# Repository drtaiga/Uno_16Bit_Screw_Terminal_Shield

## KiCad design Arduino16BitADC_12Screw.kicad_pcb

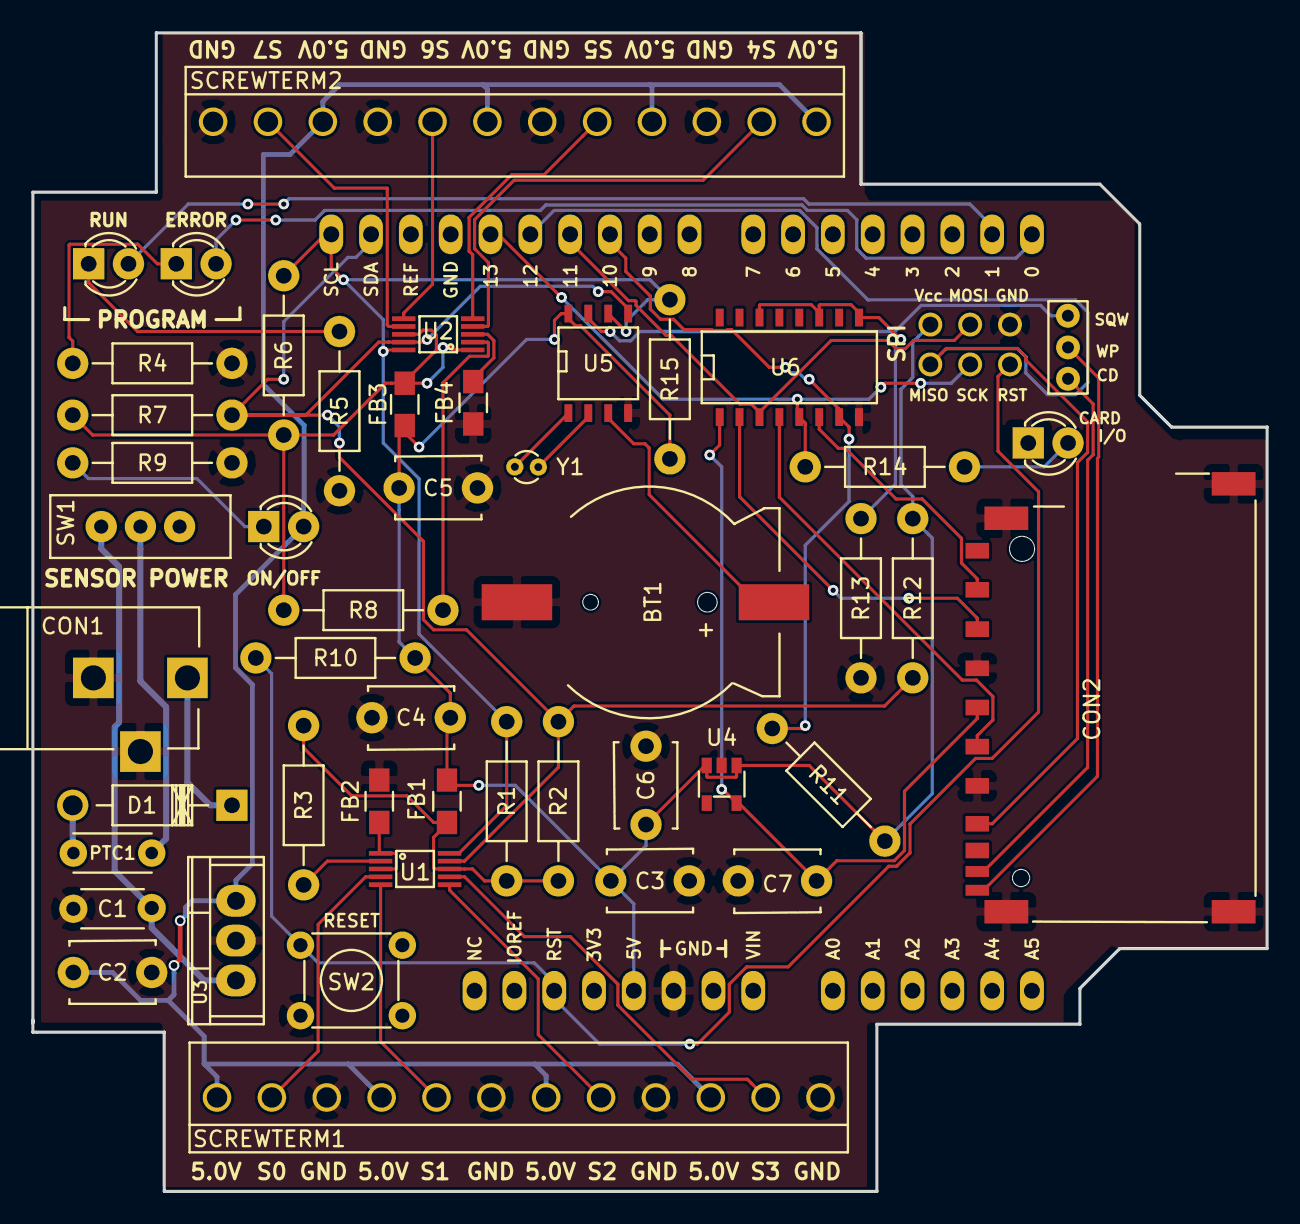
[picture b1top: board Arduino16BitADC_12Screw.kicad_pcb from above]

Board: 2 copper layers, 78.7 x 73.9 mm, 48 parts (0 on the bottom side), 45 nets.

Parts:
BT1: CR1220; Coin_Cell_Batt_12mm
C1: 0.1µF; Capacitor_4x2p5_5Pitch
C2: 10µF; Capacitor_5p5x4_5Pitch
C3, C4, C5, C6, C7: 1µF; Capacitor_5p5x4_5Pitch
CON1: BARREL_JACK; BarrelJack_PJ102A
CON2: SD_MMC; SD_101-00708-64
D1: DIODE_edit; Diode_DO-41_SOD81_Horizontal_RM10
D2, D3, D4, D5: LED; LED-3MM
FB1, FB2, FB3, FB4: Ferrite Bead; R_0805_HandSoldering
P1: CONN_01X03; Three_Hole_Jump
PTC1: PTC_Fuse; PolySwitch_PTC_Radial
R1, R2, R3, R6, R7, R8, R10, R11: 10K; Resistor_Horizontal_RM10mm
R4, R5, R9: 1K; Resistor_Horizontal_RM10mm
R12, R13, R14, R15: 2.2K; Resistor_Horizontal_RM10mm
SCREWTERM1, SCREWTERM2: TEC1776275; SCREWTERM12_3.5
SHIELD1: ARDUINO_SHIELD_VAW; ARDUINO_SHIELD_VAW_2
SW1: SWITCH_INV; Switch_EG1218
SW2: SPST; TactileSwitch_6x6mm
U1, U2: ADS115IDGST; MSOP-10
U3: LM7805CT; TO-220
U4: MIC5225_3P3; SOT23-5
U5: PCF8523; SOIC-8-N
U6: CD74HC4050; SO-16-N
Y1: 32.768kHz; Crystal_CFS-206

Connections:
/3P3V: C7.1, CON2.4, U4.5, U6.1
/5V_SENS: C2.1, D4.2, SCREWTERM1.1, SCREWTERM1.4, SCREWTERM1.7, SCREWTERM1.10, SCREWTERM2.1, SCREWTERM2.4, SCREWTERM2.7, SCREWTERM2.10, U3.3
/9V: C1.1, SW1.1, U3.1
/AIN00: SCREWTERM1.2, U1.4
/AIN01: SCREWTERM1.5, U1.5
/AIN02: SCREWTERM1.8, U1.6
/AIN03: SCREWTERM1.11, U1.7
/AIN04: SCREWTERM2.2, U2.4
/AIN05: SCREWTERM2.5, U2.5
/AIN06: SCREWTERM2.8, U2.6
/AIN07: SCREWTERM2.11, U2.7
/CD: CON2.10, P1.1
/CS: R11.2, SHIELD1.10, U6.7
/D0: D2.2, SHIELD1.0
/D1: D3.2, SHIELD1.1
/G1_GND: FB2.2, U1.1, U1.3
/G2_GND: FB4.2, U2.3
/MISO: CON2.7, SHIELD1.12, SHIELD1.SP1
/MOSI: SHIELD1.11, SHIELD1.SP4, U6.3
/RST: R10.2, SHIELD1.RST, SHIELD1.SP5, SW2.2
/SCK: R14.1, SHIELD1.13, SHIELD1.SP3, U6.5
/SCL: R1.2, R6.2, R15.2, SHIELD1.SCL, U1.10, U2.10, U5.6
/SDA: R2.2, R7.2, R12.2, SHIELD1.SDA, U1.9, U2.9, U5.5
/SD_CSIN: CON2.1, U6.6
/SD_DATIN: CON2.2, U6.2
/SD_SCKIN: CON2.5, U6.4
/SQW: P1.3, U5.7
/V1_IN: FB1.2, R1.1, R2.1, R3.1, U1.8
/V2_IN: FB3.2, R6.1, R7.1, R8.1, U2.1, U2.8
/WP: CON2.11, P1.2
GND: BT1.2, C1.2, C2.2, C3.2, C4.2, C5.2, C6.2, C7.2, CON1.2, CON1.3, CON2.3, CON2.6, CON2.12, CON2.13, CON2.14, CON2.15, D5.1, FB2.1, FB4.1, R4.2, R5.2, R9.2, R13.1, SCREWTERM1.3, SCREWTERM1.6, SCREWTERM1.9, SCREWTERM1.12, SCREWTERM2.3, SCREWTERM2.6, SCREWTERM2.9, SCREWTERM2.12, SHIELD1.GND1, SHIELD1.SP6, SW2.1, U3.2, U4.2, U5.4, U6.8
unnamed: BT1.1, U5.3
unnamed: CON1.1, D1.1
unnamed: D1.2, PTC1.1
unnamed: D2.1, R4.1
unnamed: D3.1, R5.1
unnamed: D4.1, R9.1
unnamed: D5.2, R14.2
unnamed: PTC1.2, SW1.2
unnamed: R3.2, U1.2
unnamed: R8.2, U2.2
unnamed: R13.2, U6.9, U6.11, U6.14
unnamed: U5.1, Y1.1
unnamed: U5.2, Y1.2
VCC: C3.1, C4.1, C5.1, C6.1, FB1.1, FB3.1, R10.1, R11.1, R12.1, R15.1, SHIELD1.5V, SHIELD1.SP2, U4.1, U4.3, U5.8
